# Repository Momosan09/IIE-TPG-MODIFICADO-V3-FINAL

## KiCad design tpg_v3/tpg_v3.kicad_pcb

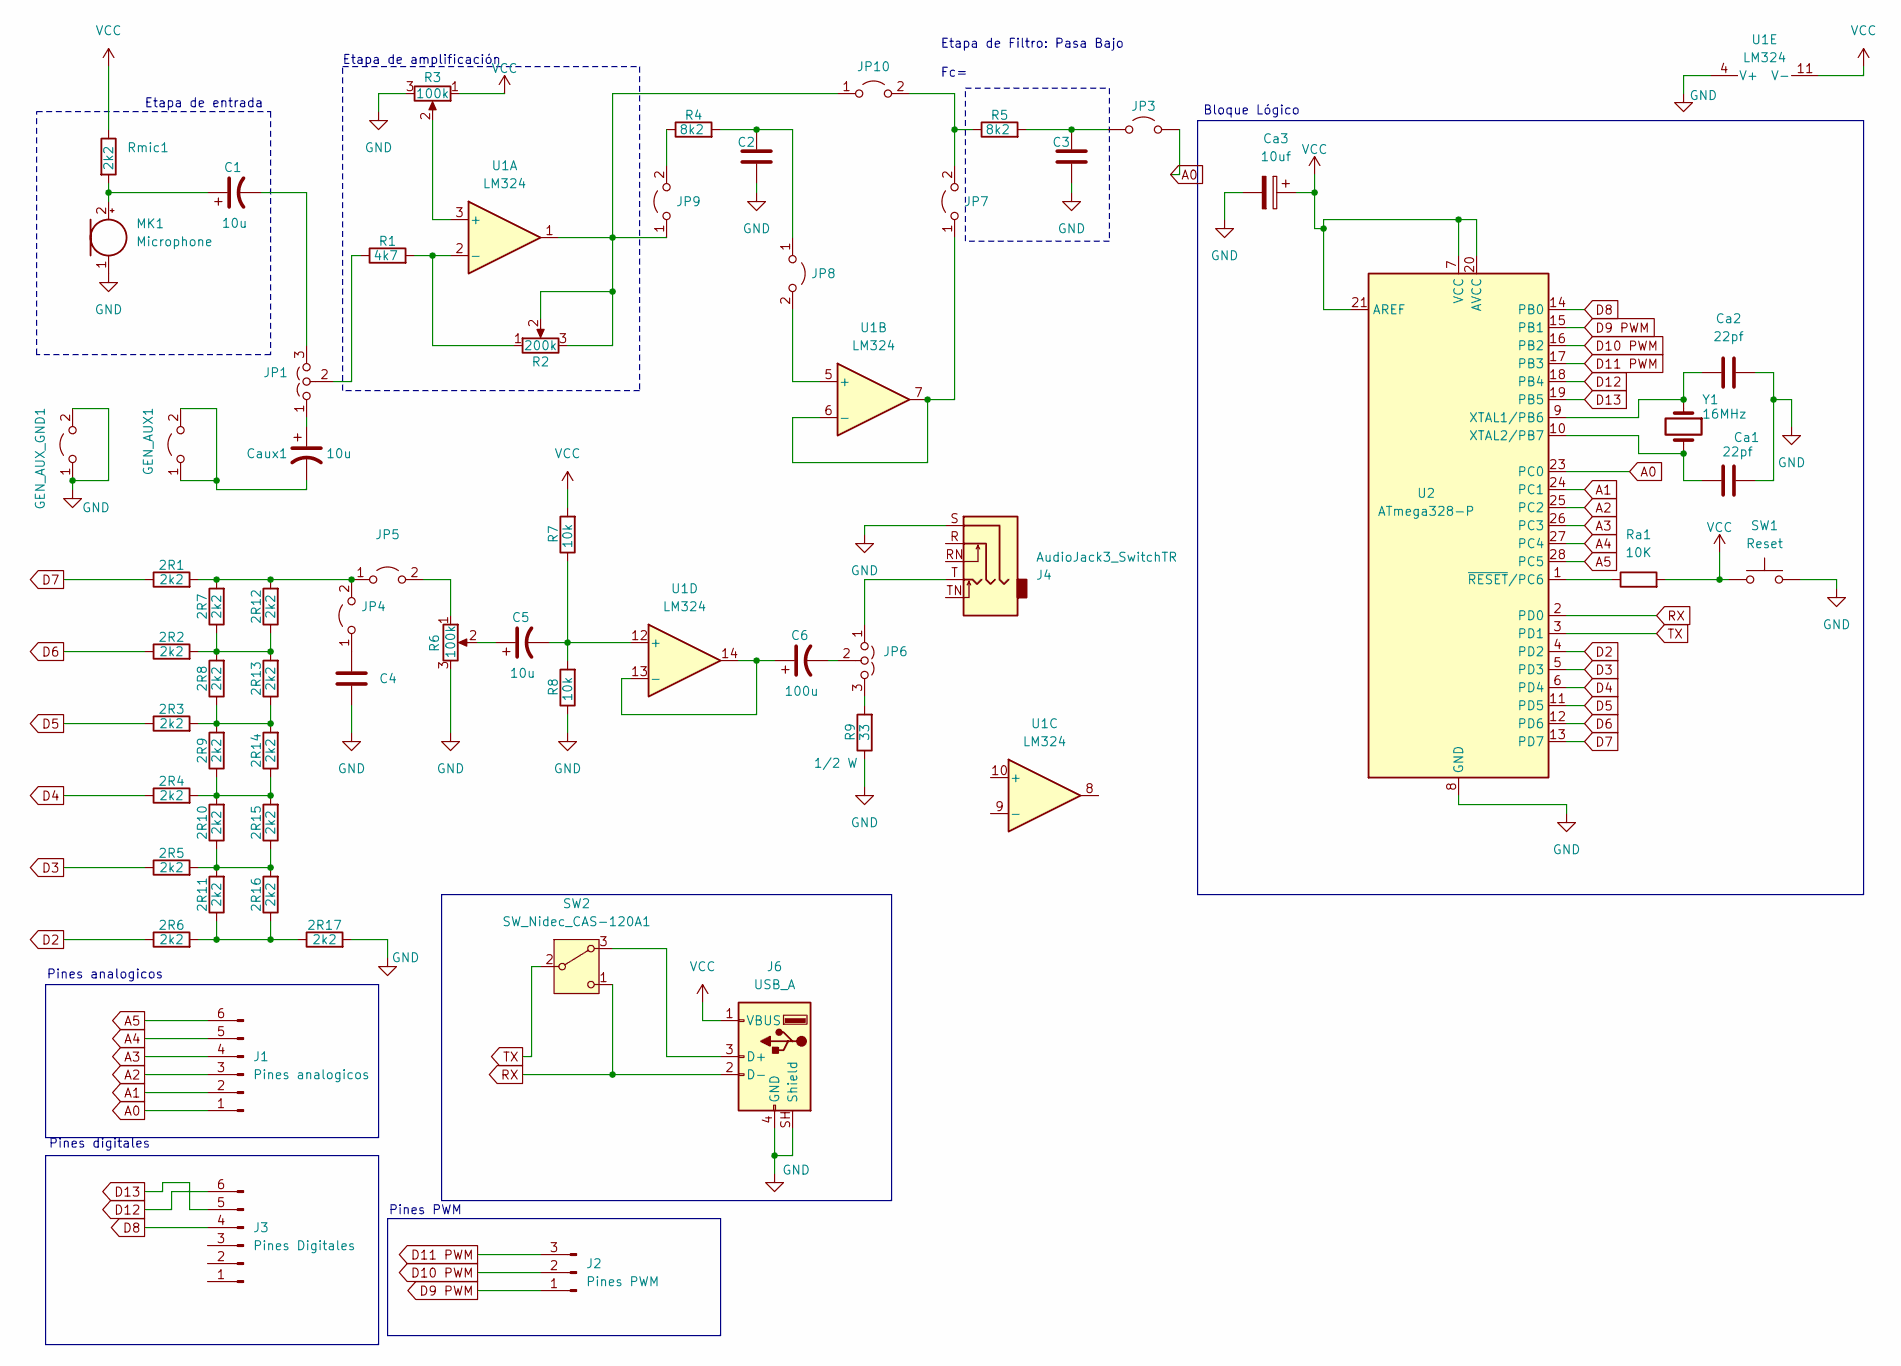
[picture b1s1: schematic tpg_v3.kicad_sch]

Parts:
2R1, 2R2, 2R3, 2R4, 2R5, 2R6, 2R7, 2R8, 2R9, 2R10, 2R11, 2R12, 2R13, 2R14, 2R15, 2R16, 2R17: 2k2; R_Axial_DIN0204_L3.6mm_D1.6mm_P5.08mm_Horizontal
C1, C5: 10u; CP_Radial_D6.3mm_P2.50mm
C2, C3, C4: C_Disc_D5.0mm_W2.5mm_P2.50mm
C6: 100u; CP_Radial_D6.3mm_P2.50mm
Ca1, Ca2: 22pf; C_Disc_D3.0mm_W1.6mm_P2.50mm
Ca3: 10uf; CP_Radial_D10.0mm_P5.00mm
Caux1: 10u; CP_Radial_D6.3mm_P2.50mm
GEN_AUX1: PinHeader_1x02_P2.54mm_Vertical
GEN_AUX_GND1: PinHeader_1x02_P2.54mm_Vertical
J1: Pines analogicos; PinHeader_1x06_P2.54mm_Vertical
J2: Pines PWM; PinHeader_1x03_P2.54mm_Vertical
J3: Pines Digitales; PinHeader_1x06_P2.54mm_Vertical
J4: AudioJack3_SwitchTR; Jack_3.5mm_CUI_SJ1-3523N_Horizontal
J6: USB_A; USB_A_Molex_67643_Horizontal
JP1, JP6: Jumper_3_Open; PinHeader_1x03_P2.54mm_Vertical
JP3, JP4, JP5, JP7, JP8, JP9, JP10: PinHeader_1x02_P2.54mm_Vertical
MK1: Microphone; PinHeader_1x02_P2.54mm_Vertical
R1: 4k7; R_Axial_DIN0204_L3.6mm_D1.6mm_P5.08mm_Horizontal
R2: 200k; Potentiometer_Bourns_3296W_Vertical
R3, R6: 100k; Potentiometer_Bourns_3296W_Vertical
R4, R5: 8k2; R_Axial_DIN0204_L3.6mm_D1.6mm_P5.08mm_Horizontal
R7, R8: 10k; R_Axial_DIN0204_L3.6mm_D1.6mm_P5.08mm_Horizontal
R9: 33; R_Axial_DIN0207_L6.3mm_D2.5mm_P10.16mm_Horizontal
Ra1: 10K; R_Axial_DIN0207_L6.3mm_D2.5mm_P10.16mm_Horizontal
Rmic1: 2k2; R_Axial_DIN0204_L3.6mm_D1.6mm_P5.08mm_Horizontal
SW1: Reset; SW_PUSH_6mm_H7.3mm
SW2: SW_Nidec_CAS-120A1; SW_CK_JS202011CQN_DPDT_Straight
U1: LM324; DIP-14_W7.62mm_LongPads
U2: ATmega328-P; DIP-28_W7.62mm
Y1: 16MHz; Crystal_HC49-4H_Vertical

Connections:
A0: J1.1, JP3.2 (B), U2.23 (PC0)
A1: J1.2, U2.24 (PC1)
A2: J1.3, U2.25 (PC2)
A3: J1.4, U2.26 (PC3)
A4: J1.5, U2.27 (PC4)
A5: J1.6, U2.28 (PC5)
D2: 2R6.1, U2.4 (PD2)
D3: 2R5.1, U2.5 (PD3)
D4: 2R4.1, U2.6 (PD4)
D5: 2R3.1, U2.11 (PD5)
D6: 2R2.1, U2.12 (PD6)
D7: 2R1.1, U2.13 (PD7)
D8: J3.4, U2.14 (PB0)
D9 PWM: J2.1, U2.15 (PB1)
D10 PWM: J2.2, U2.16 (PB2)
D11 PWM: J2.3, U2.17 (PB3)
D12: J3.6, U2.18 (PB4)
D13: J3.5, U2.19 (PB5)
GND: 2R17.2, C2.2, C3.2, C4.2, Ca1.2, Ca2.2, Ca3.2, GEN_AUX_GND1.1 (A), GEN_AUX_GND1.2 (B), J4.S, J6.4 (GND), J6.SH (Shield), MK1.1 (-), R3.3, R6.3, R8.1, R9.1, SW1.2, U1.4 (V+), U2.8 (GND), U2.22 (GND)
unnamed: 2R5.2, 2R10.1, 2R11.2, 2R15.1, 2R16.2
unnamed: 2R4.2, 2R9.1, 2R10.2, 2R14.1, 2R15.2
unnamed: 2R6.2, 2R11.1, 2R16.1, 2R17.1
unnamed: 2R2.2, 2R7.1, 2R8.2, 2R12.1, 2R13.2
unnamed: 2R3.2, 2R8.1, 2R9.2, 2R13.1, 2R14.2
unnamed: C5.1, R6.2
unnamed: Caux1.2, GEN_AUX1.1 (A), GEN_AUX1.2 (B)
unnamed: J6.3 (D+), SW2.3 (A)
unnamed: Caux1.1, JP1.1 (A)
unnamed: C1.2, JP1.3 (B)
unnamed: JP1.2 (C), R1.1
unnamed: C3.1, JP3.1 (A), R5.2
unnamed: C4.1, JP4.1 (A)
unnamed: 2R1.2, 2R7.2, 2R12.2, JP4.2 (B), JP5.1 (A)
unnamed: JP5.2 (B), R6.1
unnamed: J4.T, JP6.1 (A)
unnamed: JP6.3 (B), R9.2
unnamed: C6.2, JP6.2 (C)
unnamed: JP7.1 (A), U1.6 (-), U1.7
unnamed: C2.1, JP8.1 (A), R4.2
unnamed: JP8.2 (B), U1.5 (+)
unnamed: JP9.2 (B), R4.1
unnamed: JP9.1 (A), JP10.1 (A), R2.2, R2.3, U1.1
unnamed: JP7.2 (B), JP10.2 (B), R5.1
unnamed: C1.1, MK1.2 (+), Rmic1.2
unnamed: R3.2, U1.3 (+)
unnamed: R1.2, R2.1, U1.2 (-)
unnamed: C5.2, R7.1, R8.2, U1.12 (+)
unnamed: C6.1, U1.13 (-), U1.14
unnamed: Ca2.1, U2.9 (XTAL1/PB6), Y1.1
unnamed: Ca1.1, U2.10 (XTAL2/PB7), Y1.2
unnamed: Ra1.1, U2.1 (~RESET/PC6)
RX: J6.2 (D-), SW2.1 (C), U2.2 (PD0)
TX: SW2.2 (B), U2.3 (PD1)
VCC: Ca3.1, J6.1 (VBUS), R3.1, R7.2, Ra1.2, Rmic1.1, SW1.1, U1.11 (V-), U2.7 (VCC), U2.20 (AVCC), U2.21 (AREF)

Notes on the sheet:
Bloque Lógico
Etapa de amplificación
Pines PWM
Etapa de Filtro: Pasa Bajo Fc=
Pines analogicos
Etapa de entrada
Pines digitales

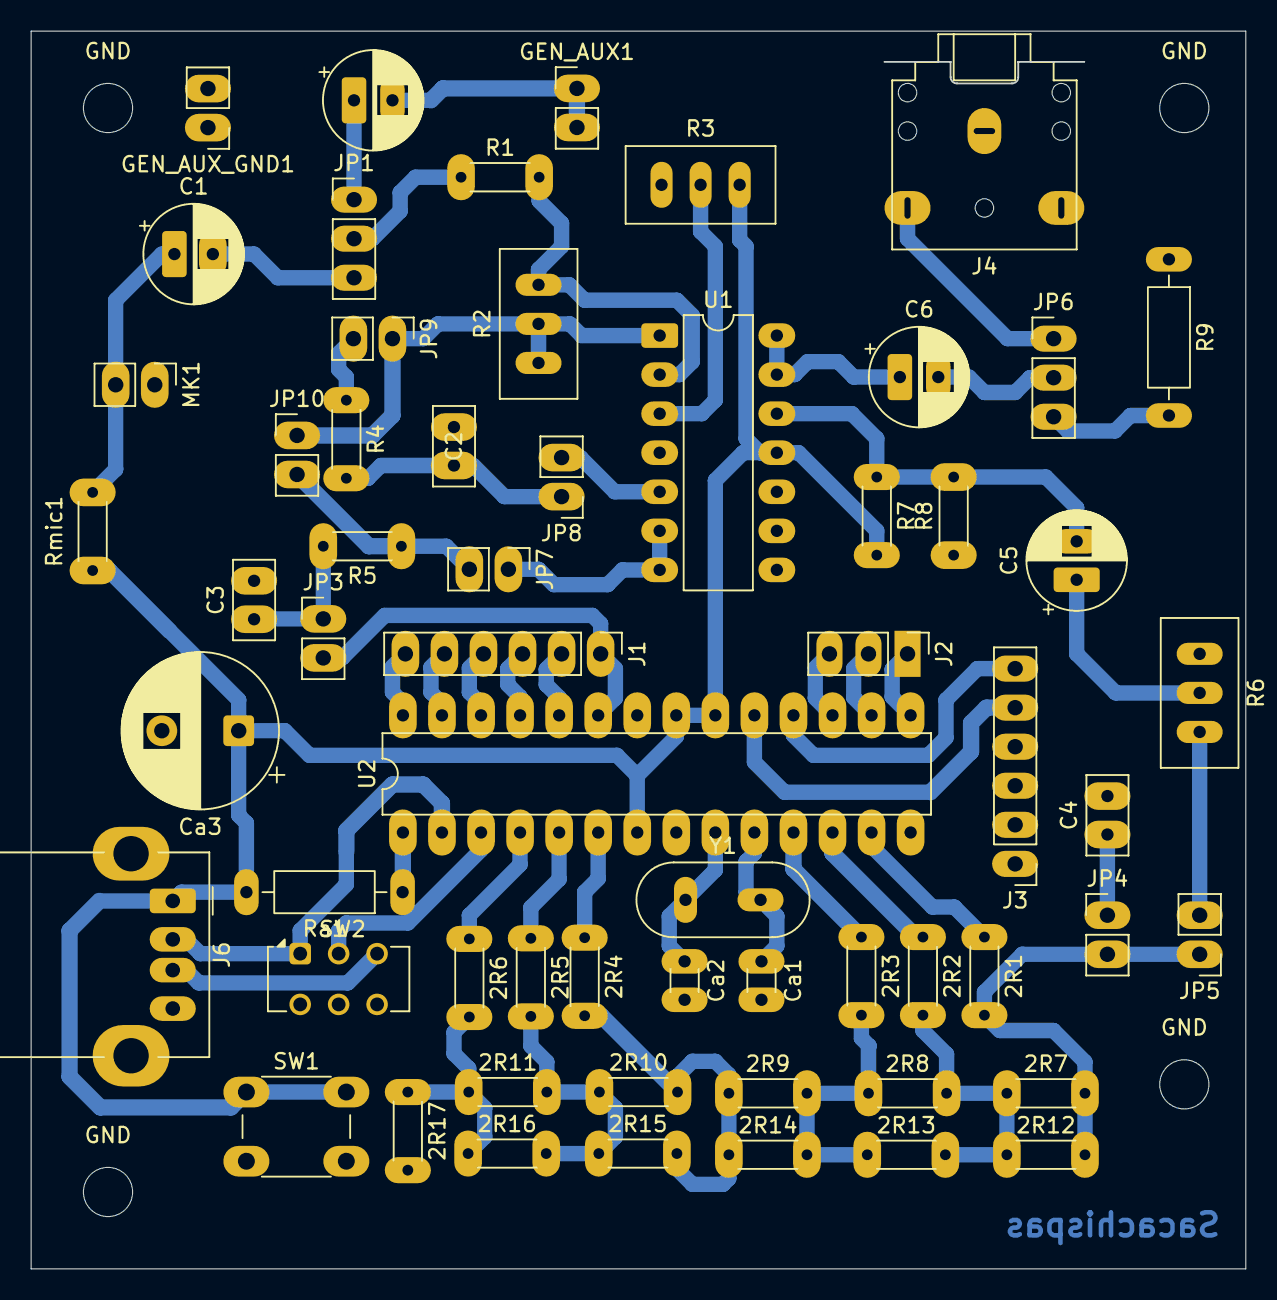
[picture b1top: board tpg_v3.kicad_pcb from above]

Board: 2 copper layers, 79.0 x 80.5 mm, 64 parts (0 on the bottom side), 54 nets.

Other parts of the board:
GND: MountingHole_3.2mm_M3_ISO14580
GND#2, GND#3, GND#4: MountingHole_3.2mm_M3_ISO14580
